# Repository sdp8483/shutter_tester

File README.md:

# Shutter Tester
Light sensor array for measuring shutter timing of SLR cameras.

## Directory Outline
- [`~/pcb/`](pcb) is for KiCAD desinge files. When starting a new KiCAD project in this directory be sure to uncheck *Create a new direcotry for the project* in the **Create New Project** window.
- [`~/firmware/`](firmware) is for firmware souce code and binaries.
- [`~/enclosure/`](enclosure) is for mechanical CAD design files for the encloser or box. Create seperate directories for `.stl` or other files for 3d printing for easy accesss.

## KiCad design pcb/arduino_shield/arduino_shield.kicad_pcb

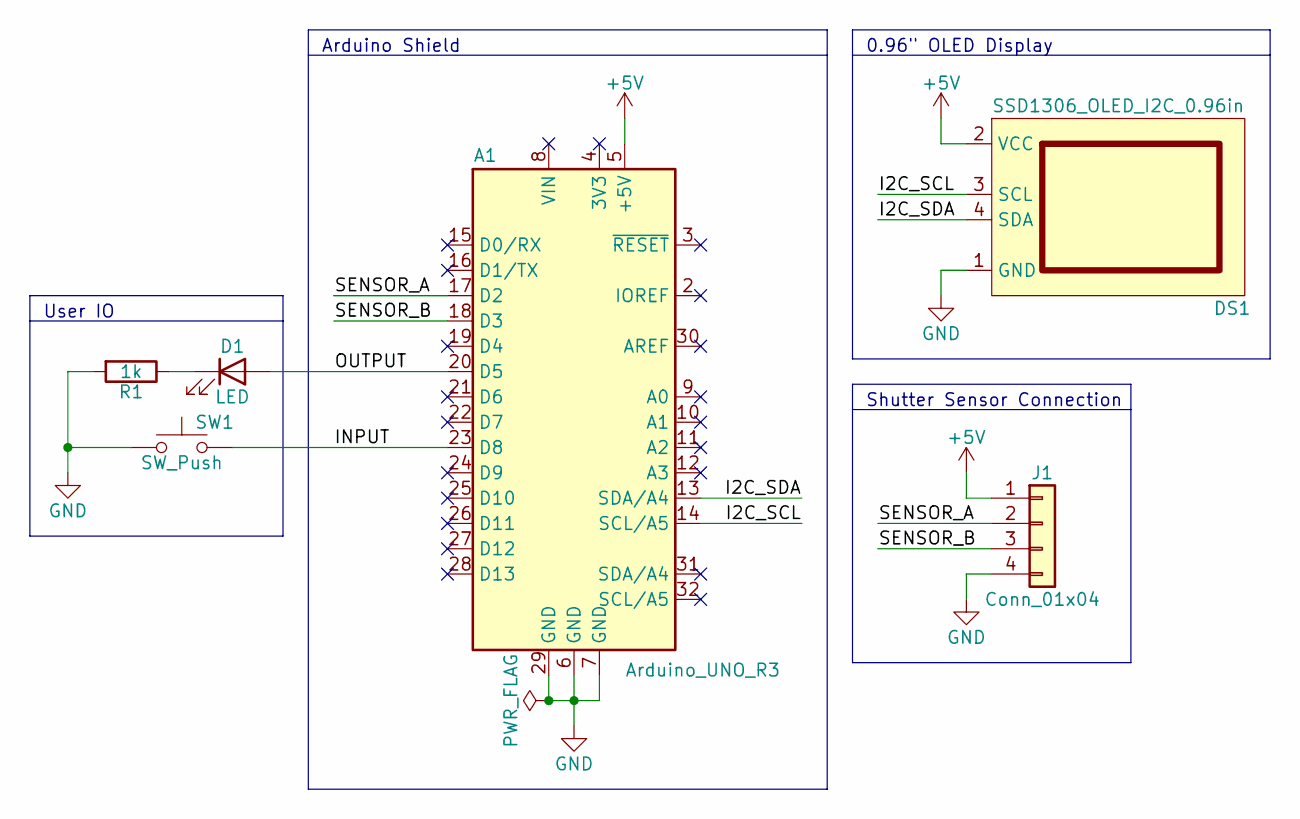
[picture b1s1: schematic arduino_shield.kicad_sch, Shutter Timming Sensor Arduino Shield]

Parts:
A1: Arduino_UNO_R3
D1: LED; LED_0805_2012Metric_Pad1.15x1.40mm_HandSolder
DS1: SSD1306_OLED_I2C_0.96in; ssd1306_oled_i2c_0.96in
J1: Conn_01x04; PinHeader_1x04_P2.54mm_Vertical
R1: 1k; R_0603_1608Metric_Pad0.98x0.95mm_HandSolder
SW1: SW_Push; SW_PUSH_6mm

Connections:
+5V: A1.5 (+5V), DS1.2 (VCC), J1.1
/I2C_SCL: A1.14 (SCL/A5), DS1.3 (SCL)
/I2C_SDA: A1.13 (SDA/A4), DS1.4 (SDA)
/INPUT: A1.23 (D8), SW1.2
/OUTPUT: A1.20 (D5), D1.2 (A)
/SENSOR_A: A1.17 (D2), J1.2
/SENSOR_B: A1.18 (D3), J1.3
GND: A1.6 (GND), A1.7 (GND), A1.29 (GND), DS1.1 (GND), J1.4, R1.2, SW1.1
unnamed: D1.1 (K), R1.1

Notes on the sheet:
User IO
Arduino Shield
Shutter Sensor Connection
0.96" OLED Display

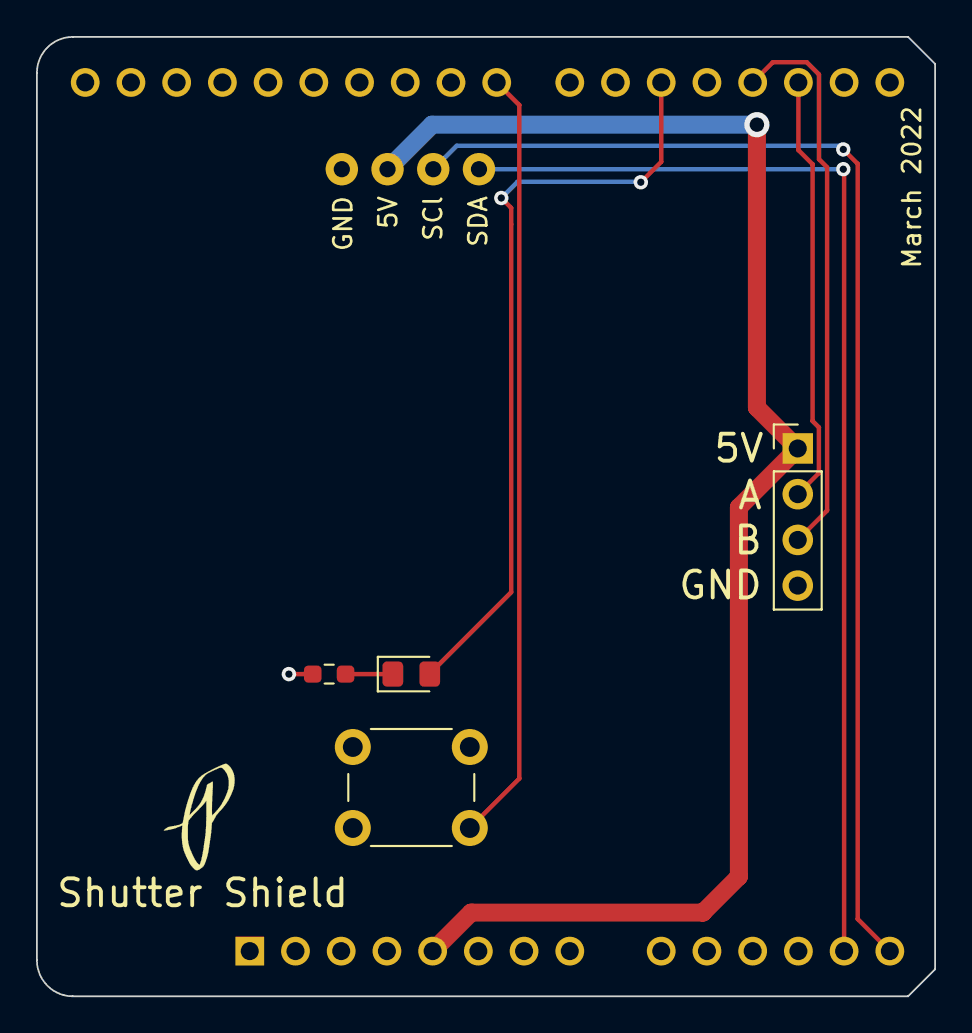
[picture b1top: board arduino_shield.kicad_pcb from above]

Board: 2 copper layers, 49.9 x 53.3 mm, 6 parts (1 on the bottom side), 9 nets.

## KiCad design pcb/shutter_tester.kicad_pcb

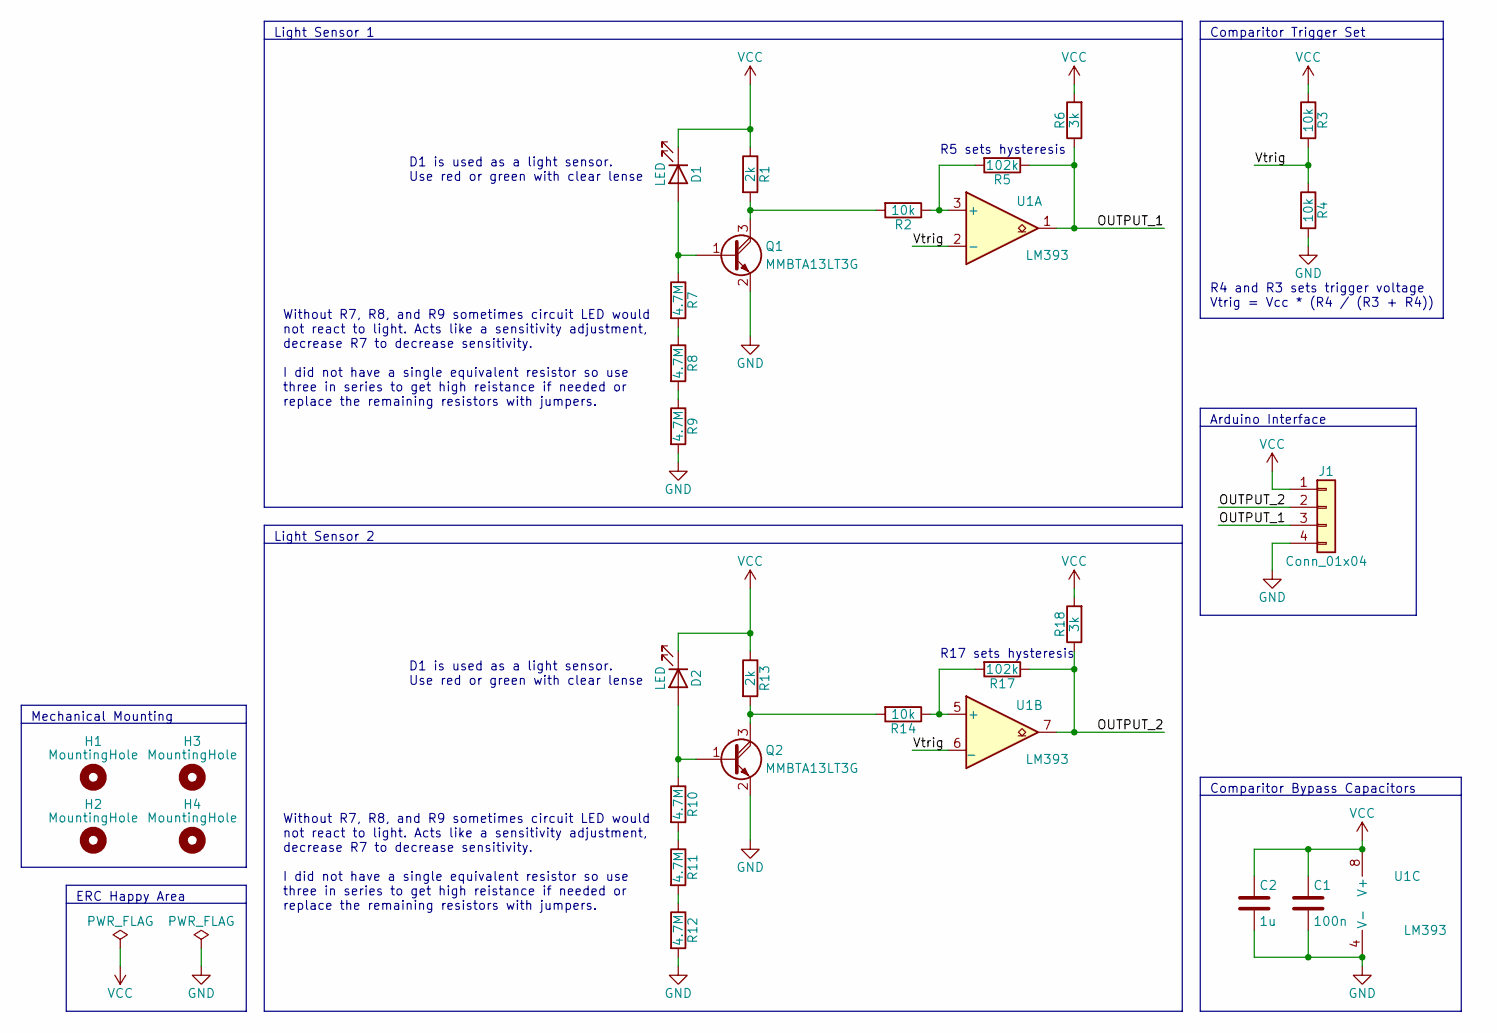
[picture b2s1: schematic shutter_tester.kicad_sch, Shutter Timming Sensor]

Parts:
C1: 100n; C_0805_2012Metric_Pad1.18x1.45mm_HandSolder
C2: 1u; C_0805_2012Metric_Pad1.18x1.45mm_HandSolder
D1, D2: LED; LED_0805_2012Metric_Pad1.15x1.40mm_HandSolder
H1, H2, H3, H4: MountingHole; MountingHole_3.2mm_M3
J1: Conn_01x04; PinHeader_1x04_P2.54mm_Vertical
Q1, Q2: MMBTA13LT3G; SOT-23
R1, R13: 2k; R_0805_2012Metric_Pad1.20x1.40mm_HandSolder
R2, R3, R4, R14: 10k; R_0603_1608Metric_Pad0.98x0.95mm_HandSolder
R5, R17: 102k; R_0603_1608Metric_Pad0.98x0.95mm_HandSolder
R6, R18: 3k; R_0805_2012Metric_Pad1.20x1.40mm_HandSolder
R7, R8, R9, R10, R11, R12: 4.7M; R_0603_1608Metric_Pad0.98x0.95mm_HandSolder
U1: LM393; SOP-8_3.9x4.9mm_P1.27mm

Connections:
/OUTPUT_1: J1.3, R5.1, R6.1, U1.1
/OUTPUT_2: J1.2, R17.1, R18.1, U1.7
/Vtrig: R3.2, R4.1, U1.2 (-), U1.6 (_)
GND: C1.2, C2.2, J1.4, Q1.2 (E), Q2.2 (E), R4.2, R9.2, R12.2, U1.4 (V-)
unnamed: D1.2 (A), Q1.1 (B), R7.1
unnamed: D2.2 (A), Q2.1 (B), R10.1
unnamed: Q1.3 (C), R1.2, R2.2
unnamed: Q2.3 (C), R13.2, R14.2
unnamed: R2.1, R5.2, U1.3 (+)
unnamed: R7.2, R8.1
unnamed: R8.2, R9.1
unnamed: R10.2, R11.1
unnamed: R11.2, R12.1
unnamed: R14.1, R17.2, U1.5 (+)
VCC: C1.1, C2.1, D1.1 (K), D2.1 (K), J1.1, R1.1, R3.1, R6.2, R13.1, R18.2, U1.8 (V+)

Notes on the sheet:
Arduino Interface
Light Sensor 1
Comparitor Trigger Set
Without R7, R8, and R9 sometimes circuit LED would not react to light. Acts like a sensitivity adjustment, decrease R7 to decrease sensitivity. I did not have a single equivalent resistor so use three in series to get high reistance if needed or replace the remaining resistors with jumpers.
R4 and R3 sets trigger voltage Vtrig = Vcc * (R4 / (R3 + R4))
Light Sensor 2
D1 is used as a light sensor. Use red or green with clear lense
R17 sets hysteresis
Comparitor Bypass Capacitors
R5 sets hysteresis
Mechanical Mounting
ERC Happy Area

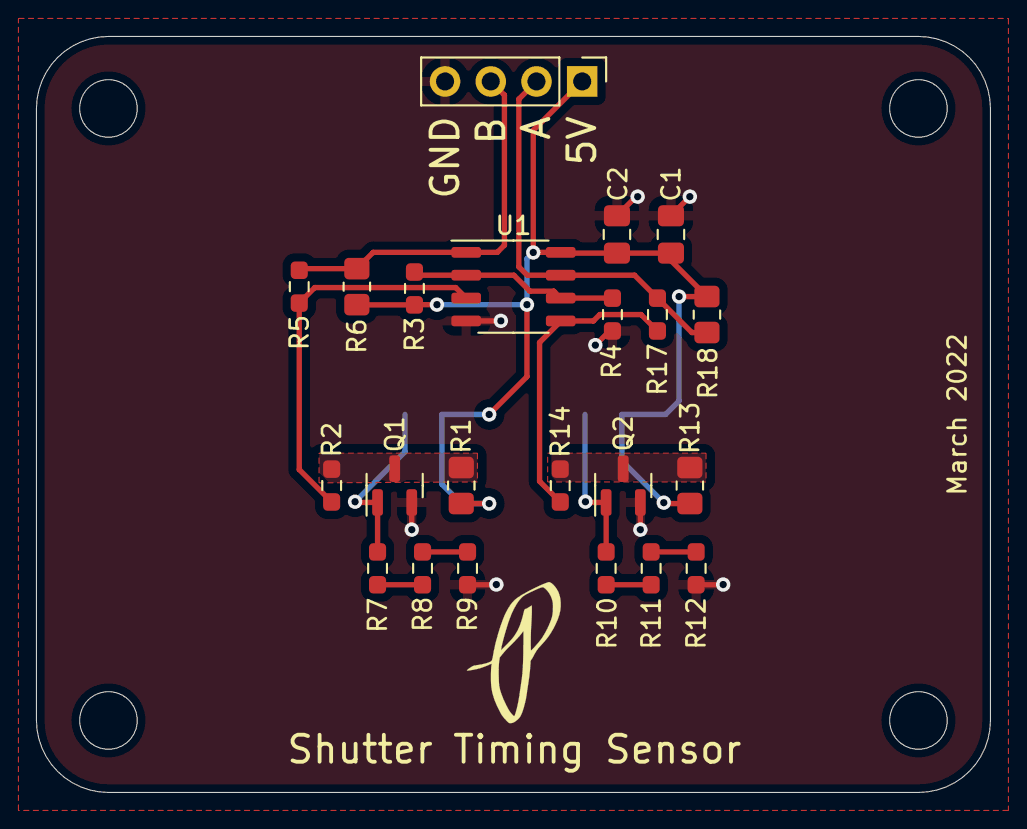
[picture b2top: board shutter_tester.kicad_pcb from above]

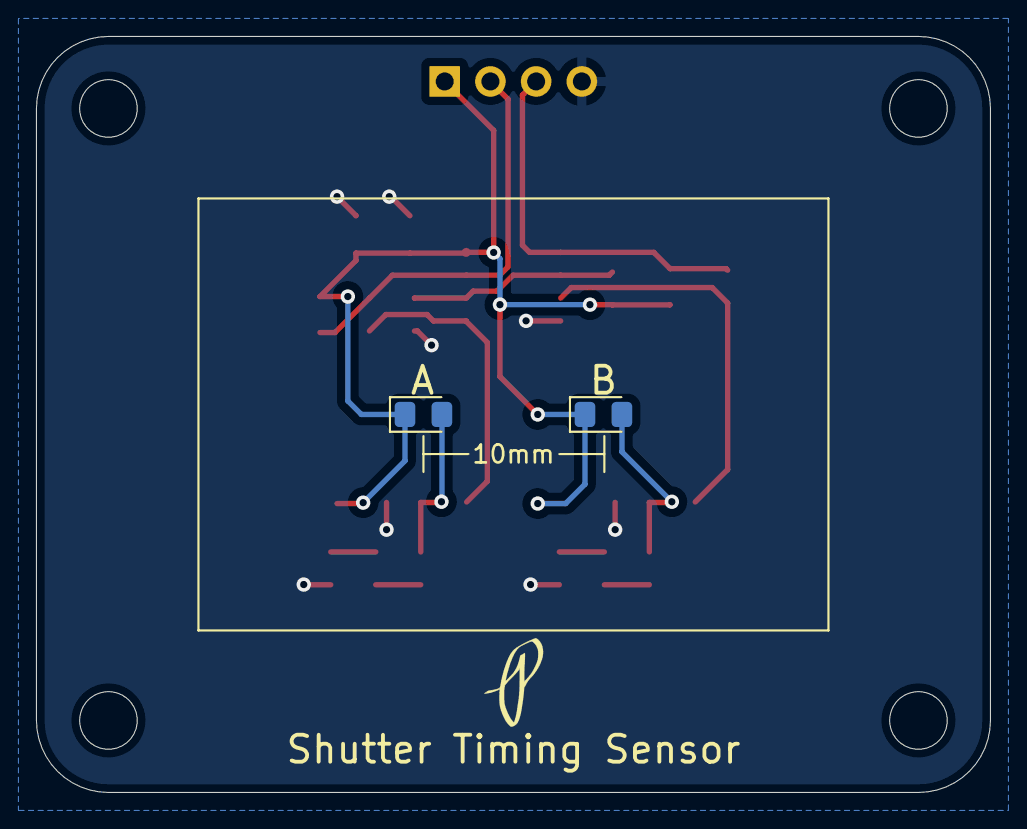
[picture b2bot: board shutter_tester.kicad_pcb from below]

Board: 2 copper layers, 53.0 x 42.0 mm, 28 parts (2 on the bottom side), 15 nets.

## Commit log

2021-08-21 init commit
2021-08-21 first draft pcb
2021-10-07 change to single light sensor
2021-10-07 generate new gcode
2021-10-11 init firmware
2021-10-12 init code
2021-10-13 clunky but working
2021-10-13 no print !
2021-10-13 new code
2021-10-16 add comparator circuit
2021-10-16 rename dir
2021-10-16 move tracks for engraving tip access
2021-10-16 export to gerber
2021-10-16 generate gcode
2021-10-16 simple cover
2021-10-16 add pulldown resistor to darlington
2021-10-16 update with new pulldown
2021-10-17 add ssd1306 display
2021-10-21 add notes to circuit
2021-10-21 output pdf
2022-02-28 zip up pcb mill version
2022-02-28 convert to kicad 6
2022-03-01 getting to rev b layout
2022-03-01 ignore backups
2022-03-01 rev a layout
2022-03-01 move to new dir
2022-03-01 new pcb
2022-03-01 shutter shield
2022-03-01 add github link
2022-03-01 export schma pdf
2022-03-01 export pcb to gerber
2022-07-20 Create fp-info-cache
